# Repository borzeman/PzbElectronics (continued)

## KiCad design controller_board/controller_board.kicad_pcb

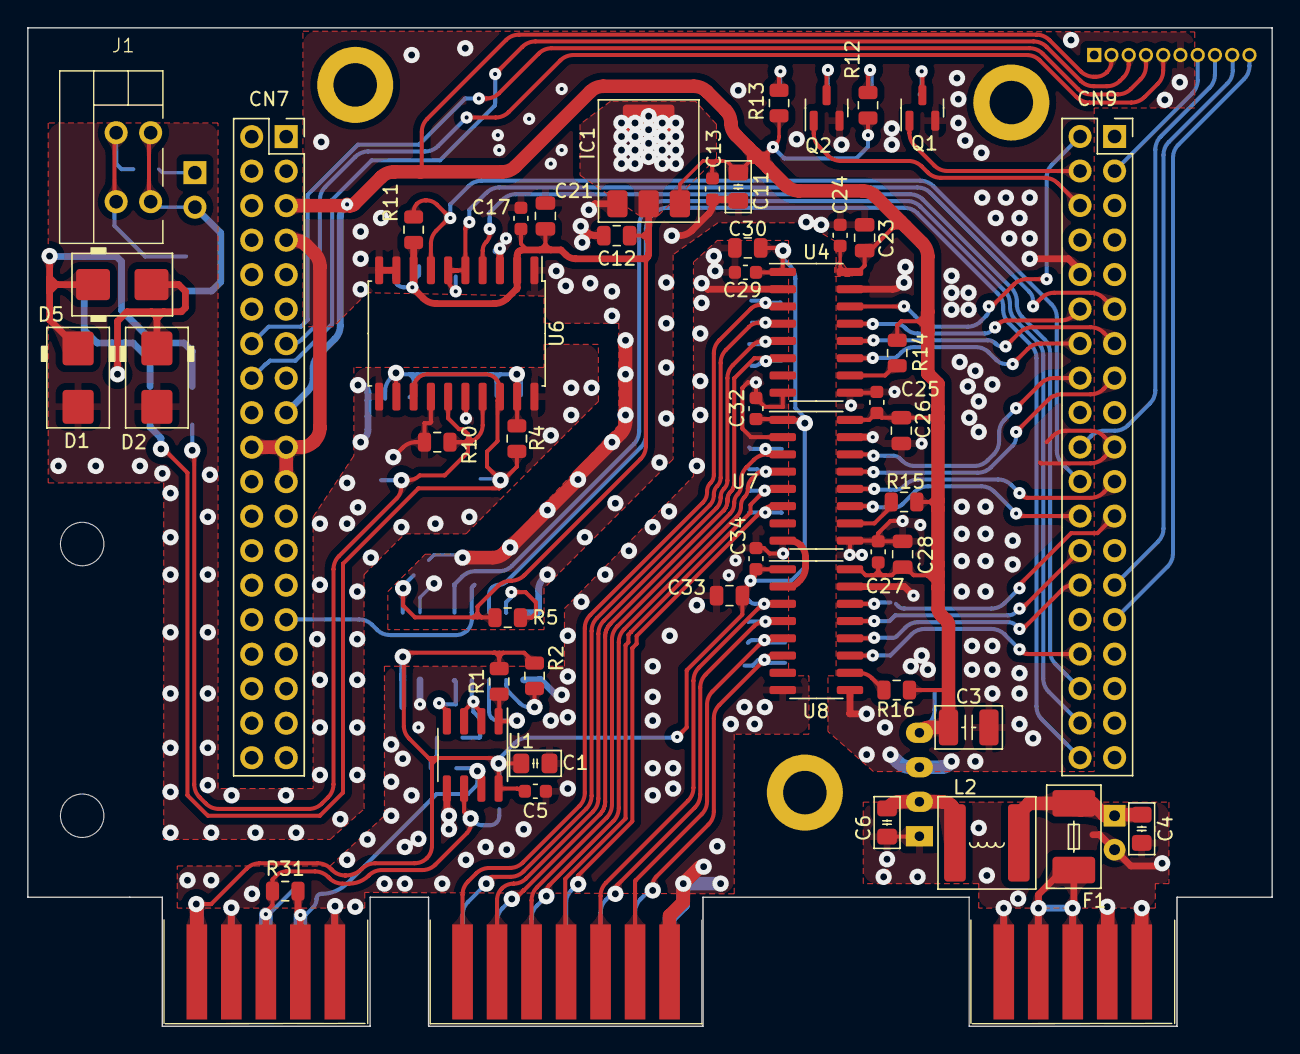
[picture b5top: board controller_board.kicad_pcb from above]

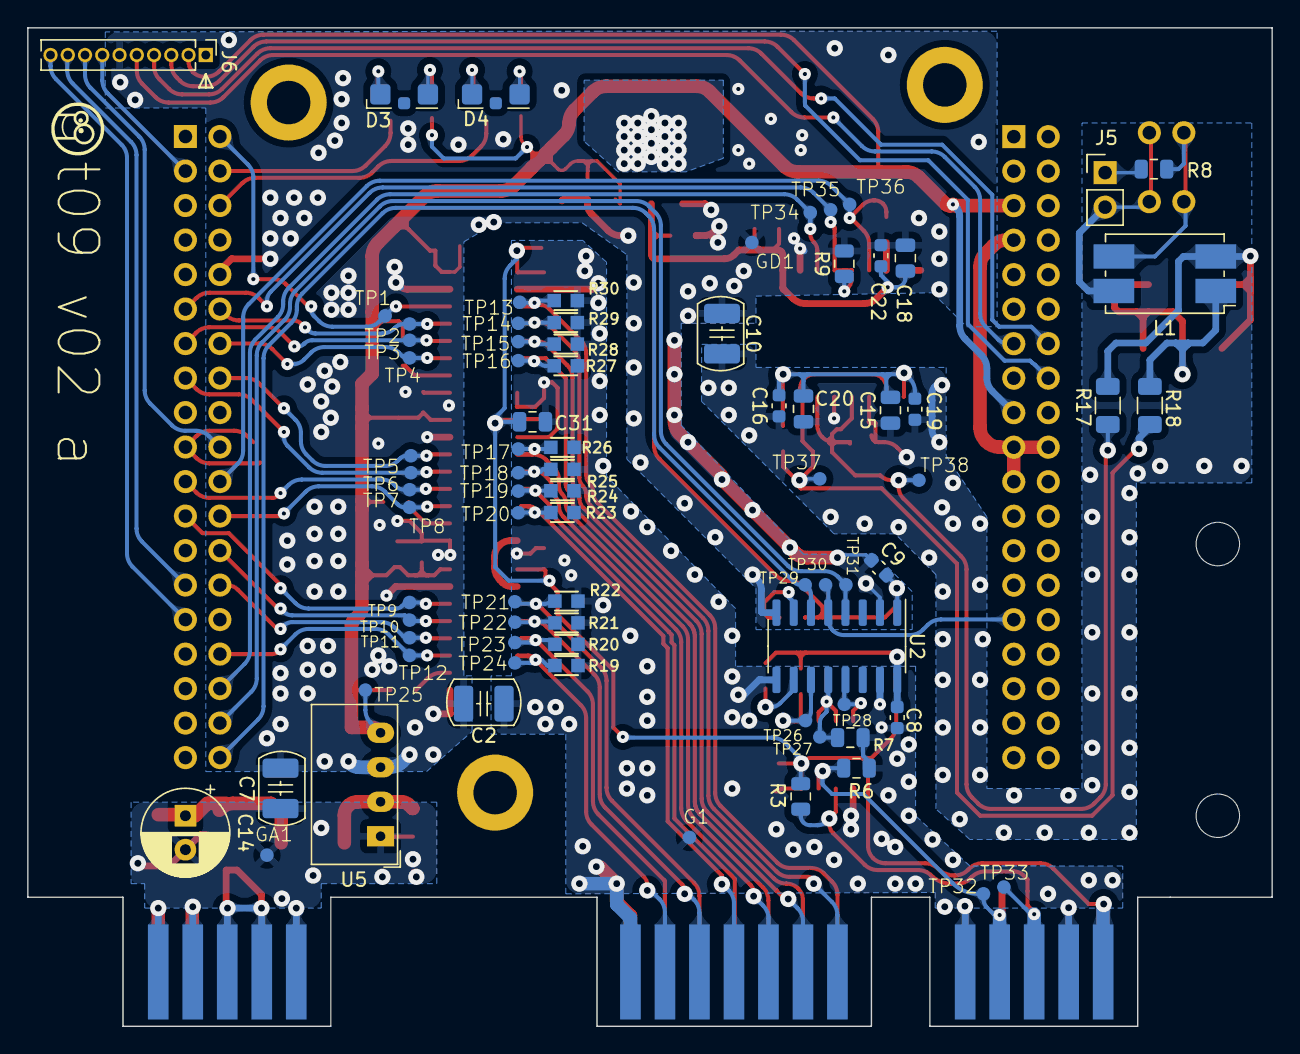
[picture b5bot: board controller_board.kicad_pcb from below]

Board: 2 copper layers, 91.6 x 73.5 mm, 137 parts (80 on the bottom side), 71 nets.

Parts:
C1, C11: 1uF 50V 0805; C_0805_2012Metric_Pad1.18x1.45mm_HandSolder
C2, C7, C10: 270 pf X7R 1206 2000v 202R18W271KW4E; C_1210_3225Metric_Pad1.42x2.65mm
C3: 10uF 50V 1210 GRM32ER71H106K; C_1210_3225Metric_Pad1.42x2.65mm_HandSolder
C4, C6: 4,7uF 50V 0805; C_0805_2012Metric_Pad1.18x1.45mm_HandSolder
C5, C8, C9, C13, C16, C17, C19, C22, C24, C25, C27, C29, C32, C34: 0,1uF 100V 0603; C_0603_1608Metric
C12, C15, C18, C23, C26, C28, C30, C31, C33: 10uF 16V 0805; C_0805_2012Metric
C14: 47uF 63V D6,3 H11; CP_Radial_D6.3mm_P2.50mm
C20, C21: 10nF 50V 0805; C_0805_2012Metric
CN7, CN9: DS1023-2x19S21; PinSocket_2x19_P2.54mm_Vertical
D1, D2: SMBJ5.0A; D_SMB
D3, D4: KPA-3010CGCK; LED_Kingbright_KPA-3010_3x2x1mm
D5: SMBJ10CA; D_SMB
F1: 0452.500MRL; Fuse_Littelfuse-NANO2-451_453
G1: TestPoint; TestPoint_D1
GA1: TestPoint; TestPoint_D1
GD1: TestPoint; TestPoint_D1
H1, H2: MountingHole; MountingHole_3.2mm_M3
H3, H4, H5: MountingHole; MountingHole_3.2mm_M3_DIN965_Pad
IC1: LD1117-3.3V-SOT223; SOT-223-3_TabPin2
J1: DG141R-02 (RS485); DG141R-02
J5: DS1027-2B и PinHeader_2x01_P2.54mm; PinHeader_1x02_P2.54mm_Vertical
J6: PLL-10 (Prog); PinHeader_1x10_P1.27mm_Vertical
L1: B82790S0253N201; L_CommonMode_Delevan_4222
L2: 6,8uH 3,5A (ETQP3M6R8KVP); L_Bourns-SRN6028
Q1, Q2: DTC114ECA (SOT-23); SOT-23
R1, R7, R9, R11: 0805-10 кОм±5%-0,125 Вт; R_0805_2012Metric
R2, R5: 0805-4,7 кОм±5%-0,125 Вт; R_0805_2012Metric
R3, R6: 0805-430 Ом±5%-0,125 Вт; R_0805_2012Metric
R4, R10: 0805-560 Ом±5%-0,125 Вт; R_0805_2012Metric
R8, R31: 0805 -120 Ом±5%-0,125 Вт; R_0805_2012Metric
R12, R13: 0805-300 Ом±5%-0,125 Вт; R_0805_2012Metric
R14, R15, R16: 0805-100 Ом±5%-0,125 Вт; R_0805_2012Metric
R17, R18: 1206-100 Ом±5%-0,25 Вт; R_1206_3216Metric
R19, R20, R21, R22, R23, R24, R25, R26, R27, R28, R29, R30: 0603-10 кОм±5%-0,062 Вт; R_0603
RS1, RS2: SL-10 (L-KLS1-603C-10-S); Edge_Conn_KLS1-603-10
RS3: SL-14 (L-KLS1-603C-14-S) RTS; Edge_Conn_KLS1-603-14
TP1, TP2, TP3, TP4, TP5, TP6, TP7, TP8, TP9, TP10, TP11, TP12, TP13, TP14, TP15, TP16, TP17, TP18, TP19, TP20, TP21, TP22, TP23, TP24, TP25, TP26, TP27, TP28, TP29, TP30, TP31, TP32, TP33, TP34, TP35, TP36, TP37, TP38: TestPoint; TestPoint_D1
U1: ADM3485EARZ-REEL (SOIC-8); SOIC-8_3.9x4.9mm_P1.27mm
U2: pia141M30 (SOIC-16); SOIC-16_3.9x9.9mm_P1.27mm
U4, U7, U8: pia140M30 (SOIC-16); SOIC-16_3.9x9.9mm_P1.27mm
U5: SMU02N-05; Converter_DCDC_Murata_CRE1xxxxxxSC_THT
U6: ADM2587E (SOIC-20); SOIC-20W_7.5x12.8mm_P1.27mm

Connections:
+3V3: C9.2, C12.1, C17.2, C18.2, C21.2, C22.1, IC1.2 (OUT), R5.1, R11.1, U2.1 (VDD1), U6.2 (VCC), U6.8 (VCC)
+5V: C3.1, C11.1, C13.1, C23.2, C24.1, C25.1, C26.2, C27.1, C28.2, CN7.5, CN7.17, IC1.3 (IN), J6.2, R12.2, R13.1, R14.1, R15.1, R16.1, TP25.1, U4.16 (VDD2), U5.4 (OUT+), U7.16 (VDD2), U8.16 (VDD2)
+24V: C4.1, C14.1, F1.2, L2.1
/+3.3VRS485: C1.2, C5.2, C8.2, C29.1, C30.2, C31.2, C32.1, C33.2, C34.1, R1.2, R2.2, R3.2, RS1.1, RS1.10, U1.8 (VCC), U2.16 (VDD2), U4.1 (VDD1), U7.1 (VDD1), U8.1 (VDD1)
/LED1: CN9.4, Q1.1 (B)
/LED2: CN9.6, Q2.1 (B)
/NUCLEO-64F411/GPIO1: CN9.27, J6.9
/NUCLEO-64F411/GPIO2: CN9.29, J6.10
/NUCLEO-64F411/RESET: CN7.13, J6.5
/NUCLEO-64F411/SWCLK: CN7.16, J6.3
/NUCLEO-64F411/SWDIO: CN7.14, J6.4
/NUCLEO-64F411/USART6_RX: CN9.20, J6.8
/NUCLEO-64F411/USART6_TX: CN9.3, J6.7
/RTS1: R30.1, RS3.1, TP13.1, U4.3 (VIA)
/RTS1_cont: CN9.2, TP1.1, U4.14 (VOA)
/RTS2: R29.1, RS3.14, TP14.1, U4.4 (VIB)
/RTS2_cont: CN9.12, TP2.1, U4.13 (VOB)
/RTS3: R28.1, RS3.2, TP15.1, U4.5 (VIC)
/RTS3_cont: CN9.13, TP3.1, U4.12 (VOC)
/RTS4: R27.1, RS3.13, TP16.1, U4.6 (VID)
/RTS4_cont: CN9.14, TP4.1, U4.11 (VOD)
/RTS5: R26.1, RS3.3, TP17.1, U7.3 (VIA)
/RTS5_cont: CN9.16, TP5.1, U7.14 (VOA)
/RTS6: R25.1, RS3.12, TP18.1, U7.4 (VIB)
/RTS6_cont: CN9.15, TP6.1, U7.13 (VOB)
/RTS7: R24.1, RS3.4, TP19.1, U7.5 (VIC)
/RTS7_cont: CN9.21, TP7.1, U7.12 (VOC)
/RTS8: R23.1, RS3.11, TP20.1, U7.6 (VID)
/RTS8_cont: CN9.24, TP8.1, U7.11 (VOD)
/RTS9: R22.1, RS3.5, TP21.1, U8.3 (VIA)
/RTS9_cont: CN9.23, TP9.1, U8.14 (VOA)
/RTS10: R21.1, RS3.10, TP22.1, U8.4 (VIB)
/RTS10_cont: CN9.26, TP10.1, U8.13 (VOB)
/RTS11: R20.1, RS3.6, TP23.1, U8.5 (VIC)
/RTS11_cont: CN9.28, TP11.1, U8.12 (VOC)
/RTS12: R19.1, RS3.9, TP24.1, U8.6 (VID)
/RTS12_cont: CN9.32, TP12.1, U8.11 (VOD)
/USART1_RTS: CN9.11, R9.1, TP35.1, U6.5 (~RE), U6.6 (DE)
/USART1_RX: CN9.34, TP34.1, U6.4 (RxD)
/USART1_TX: CN9.22, R11.2, TP36.1, U6.7 (TxD)
/USART2_RTS: CN7.29, TP30.1, U2.5 (VIC)
/USART2_RX: CN9.38, TP29.1, U2.6 (VOD)
/USART2_TX: CN9.36, TP31.1, U2.4 (VIB)
GND1: C1.1, C2.1, C5.1, C8.1, C29.2, C30.1, C31.1, C32.2, C33.1, C34.2, G1.1, R6.1, R7.1, R19.2, R20.2, R21.2, R22.2, R23.2, R24.2, R25.2, R26.2, R27.2, R28.2, R29.2, R30.2, RS1.2, RS1.5, RS1.6, RS1.9, RS3.7, RS3.8, U1.5 (GND), U2.9 (GND2), U2.15 (GND2), U4.2 (GND1), U4.8 (GND1), U7.2 (GND1), U7.8 (GND1), U8.2 (GND1), U8.8 (GND1)
GND2: C10.2, C15.1, C16.1, C19.1, C20.1, D1.2 (A), D2.2 (A), R10.1, U6.11 (GND2), U6.14 (GND2), U6.16 (GND2), U6.20 (GND2)
GNDA: C4.2, C6.2, C7.1, C14.2, GA1.1, RS2.1, RS2.4, RS2.5, RS2.6, RS2.7, RS2.10, U5.1 (IN-)
GNDD: C2.2, C3.2, C7.2, C9.1, C10.1, C11.2, C12.2, C13.2, C17.1, C18.1, C21.1, C22.2, C23.1, C24.2, C25.2, C26.1, C27.2, C28.1, CN7.7, CN7.19, CN7.20, CN7.21, CN9.10, CN9.19, GD1.1, IC1.1 (ADJ), J6.6, Q1.2 (E), Q2.2 (E), R9.2, U2.2 (GND1), U2.8 (GND1), U4.9 (GND2), U4.15 (GND2), U5.3 (OUT-), U6.1 (GND1), U6.3 (GND1), U6.9 (GND1), U6.10 (GND1), U7.9 (GND2), U7.15 (GND2), U8.9 (GND2), U8.15 (GND2)
unnamed: D1.1 (K), D5.1 (K), L1.2, R18.1
unnamed: D2.1 (K), D5.2 (A), L1.1, R17.2
unnamed: D3.2 (A), R12.1
unnamed: D3.1 (K), Q1.3 (C)
unnamed: D4.2 (A), R13.2
unnamed: D4.1 (K), Q2.3 (C)
unnamed: J1.1, J5.2, L1.4
unnamed: J1.2, L1.3, R8.1
unnamed: J5.1, R8.2
unnamed: R3.1, R31.2, RS1.3, RS1.8, TP33.1, U1.6 (A)
unnamed: R6.2, R31.1, RS1.4, RS1.7, TP32.1, U1.7 (B)
unnamed: F1.1, RS2.2, RS2.3, RS2.8, RS2.9
unnamed: R7.2, TP27.1, U1.2 (~RE), U1.3 (DE), U2.12 (VOC)
unnamed: TP28.1, U1.4 (DI), U2.13 (VOB)
unnamed: R1.1, TP26.1, U1.1 (RO), U2.11 (VID)
unnamed: R5.2, U2.7 (VE1)
unnamed: R2.1, U2.10 (VE2)
unnamed: R14.2, U4.10 (VE2)
unnamed: C6.1, L2.2, U5.2 (IN+)
unnamed: R4.2, R17.1, TP37.1, U6.13 (Y), U6.18 (A)
unnamed: R10.2, R18.2, TP38.1, U6.15 (Z), U6.17 (B)
unnamed: C15.2, C16.2, C19.2, C20.2, R4.1, U6.12 (Visoout), U6.19 (Visoin)
unnamed: R15.2, U7.10 (VE2)
unnamed: R16.2, U8.10 (VE2)
